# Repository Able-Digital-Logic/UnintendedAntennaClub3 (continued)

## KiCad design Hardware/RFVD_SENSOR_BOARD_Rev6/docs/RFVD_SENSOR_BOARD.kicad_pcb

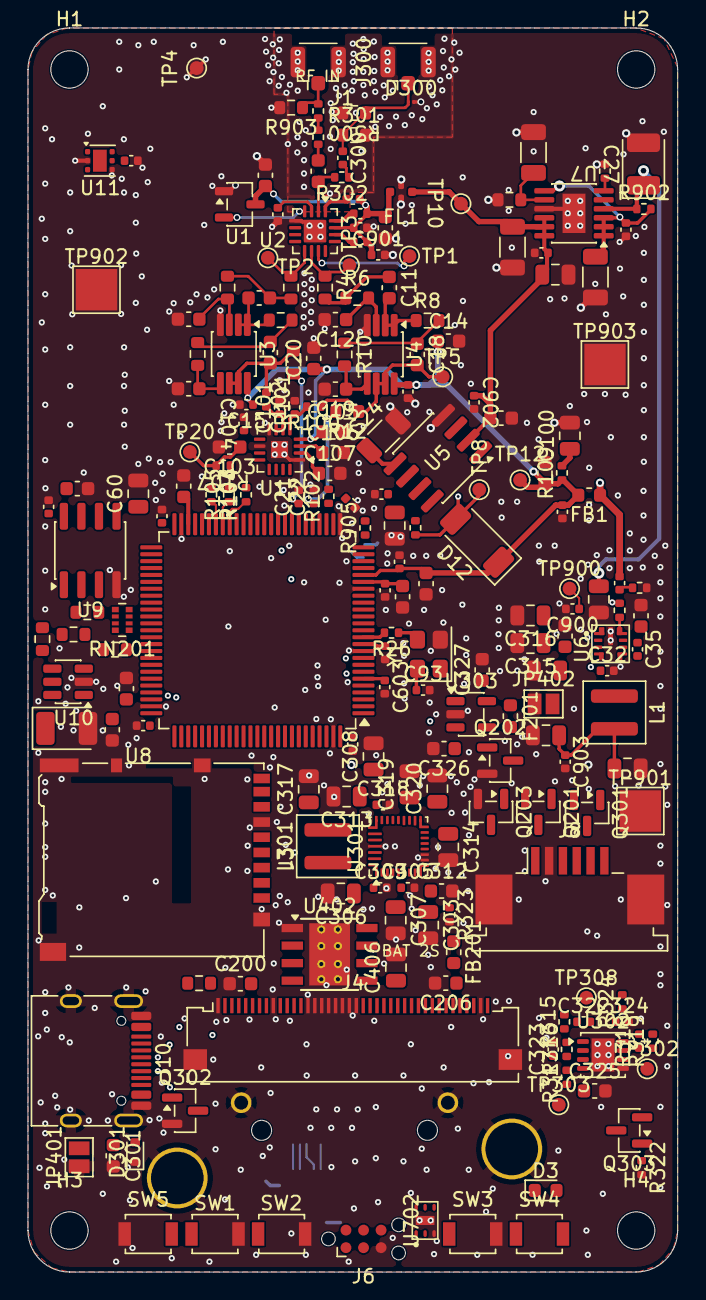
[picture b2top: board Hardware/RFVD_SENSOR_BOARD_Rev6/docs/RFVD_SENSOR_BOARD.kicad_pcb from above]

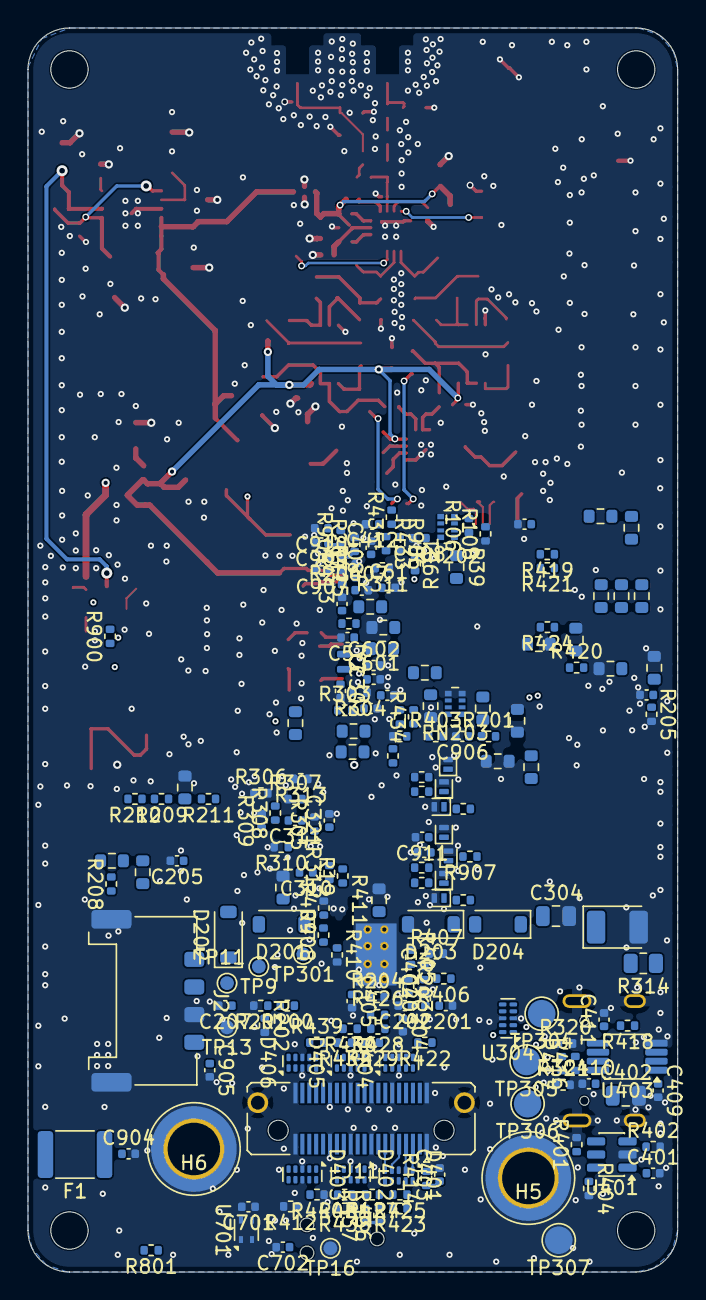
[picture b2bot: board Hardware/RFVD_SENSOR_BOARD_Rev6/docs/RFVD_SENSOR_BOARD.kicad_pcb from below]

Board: 6 copper layers, 47.0 x 90.0 mm, 409 parts (193 on the bottom side), 247 nets.

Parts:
C1, C33: 100nF; C_0603_1608Metric
C2: 47pF C0G 1% 100V; C_0603_1608Metric
C3, C4: 100pF; C_0402_1005Metric
C5, C23, C37, C44, C51, C59, C65, C103, C105, C106, C107, C301, C326: 1uF; C_0603_1608Metric
C6, C8, C321, C412: 1nF; C_0402_1005Metric
C7, C26, C29, C35, C40, C45, C46, C47, C48, C50, C53, C54, C55, C56, C57, C58, C61, C62, C64, C93, C104, C302, C305, C309, C318, C322, C323, C324, C401, C403, C404, C407, C408, C409, C410, C411, C603, C701, C702: 100nF; C_0402_1005Metric
C9, C11: 510p; C_0603_1608Metric
C10, C12, C17, C19: 470p; C_0603_1608Metric
C13, C15: 100n; C_0402_1005Metric
C14, C20: 1u; C_0603_1608Metric
C16, C18: 1.2n; C_0603_1608Metric
C21, C22: 1.5nF C0G 2% 50V; C_0402_1005Metric
C24: 1uF 25V film; C_1206_3216Metric
C25: 4.7uF; C_0805_2012Metric
C27: 22uF 25V polymer; CP_EIA-3528-21_Kemet-B
C28, C30, C38, C303, C304, C306, C307, C308, C313, C314, C315, C316, C317, C319, C320, C402, C406: 10uF; C_0805_2012Metric
C31: 10uF; C_1206_3216Metric
C32, C67, C70, C71, C205, C901, C902, C903, C904: 100nF 25V X7R; C_0402_1005Metric
C34: 470nF; C_1206_3216Metric
C36: 22uF; C_1206_3216Metric
C39, C42, C100: 22uF; C_0805_2012Metric
C41: 22pF; C_0402_1005Metric
C49, C52: 2.2uF; C_0603_1608Metric
C60: 10uF 16V X7R; C_0805_2012Metric
C63: 47uF POLY; CP_EIA-3528-21_Kemet-B
C66: 1uF 25V X7R; C_0603_1608Metric
C68: 47uF 10V POLY; CP_EIA-3528-21_Kemet-B
C69, C201: 100nF 25V; C_0402_1005Metric
C101, C102: 2.2nF C0G; C_0402_1005Metric
C200, C206: 1uF 25V; C_0603_1608Metric
C202, C203, C900: 47pF 50V C0G; C_0402_1005Metric
C204: DNP 47pF C0G; C_0402_1005Metric
C207: 100pF 50V C0G; C_0402_1005Metric
C300, C905, C906, C907: 1nF C0G 50V; C_0402_1005Metric
C310, C311, C405: 47nF; C_0402_1005Metric
C312, C327: 4.7uF; C_0603_1608Metric
C325: 330nF; C_0603_1608Metric
C601, C602: 10pF C0G; C_0402_1005Metric
C908, C909, C910: 100pF C0G 50V; C_0402_1005Metric
C911: 15pF C0G 50V; C_0402_1005Metric
D1, D300: PESD5V0H1BSF; PESD2V5Y1BSF_SOD962-2_ManufacturerLand
D3: GREEN LED; LED_0603_1608Metric
D4, D5, D6, D7, D8, D9, D10: 5V ESD 2pF; D_SOD-882
D12: PMEG6030EP; D_SOD-128
D201, D202, D203, D204: NSI45020A; D_SOD-123
D301: TPD1E10B06DYAR; D_SOD-523
D401, D402, D403, D404, D405, D406: TPD4E05U06DQAR; USON-10_2.5x1.0mm_P0.5mm
F1: MF-MSMF150/24X-2; Fuse_1812_4532Metric
F201: 200mA PTC; Fuse_0603_1608Metric
FB1: 600R@100MHz 500mA; L_0603_1608Metric
FB201: 600R@100MHz; L_0603_1608Metric
FL1: NFM18PC104R1C3D; Murata_NFM18PC_0603_3T
H1, H2, H3, H4: MountingHole_2.7mm
H5, H6: BSMTSOM250BTR; Standoff_SMT_M2_BZXC_BSMTSOM2_Hole3.8mm_Pad6.2mm
J1: AIMD_IN; U.FL_Hirose_U.FL-R-SMT-1_Vertical
J2: 2053380004; Molex_Pico-Lock_205338-0004_1x04-1MP_P2.00mm_Horizontal
J3: DM3AT-SF-PEJM5; microSD_HC_Hirose_DM3AT-SF-PEJM5
J4: XF2M-4015-1A; Omron_XF2M-4015-1A_1x40-1MP_P0.5mm_Horizontal
J6: TC2030-NL SWD POGO DNP; Tag-Connect_TC2030-IDC-NL_2x03_P1.27mm_Vertical
J8: 84953-6; TE_84953-6_1x06-1MP_P1.0mm_Horizontal
J10: TYPE-C-31-M-12; USB_C_Receptacle_HRO_TYPE-C-31-M-12
J11: LSHM-120-02.5-L-DV-A-N-K-TR; Samtec_LSHM-120-xx.x-x-DV-S_2x20-1SH_P0.50mm_Vertical
J300: CAL_IN; U.FL_Hirose_U.FL-R-SMT-1_Vertical
JP401, JP402: SJ open; SolderJumper-2_P1.3mm_Open_Pad1.0x1.5mm
L1: 4.7uH; L_Coilcraft_XAL4020-XXX
L301: 1uH; L_Coilcraft_XAL4020-XXX
Q201, Q303: AO3401A; SOT-23
Q202, Q302: 2N7002; SOT-23
Q203, Q301: AO3400A; SOT-23
R1, R2, R410: 1.50k; R_0402_1005Metric
R3, R4, R5, R6: 2.26k; R_0603_1608Metric
R7, R8, R9, R10: 1.33k; R_0603_1608Metric
R11, R12: 47R; R_0603_1608Metric
R13, R902, R907: 1R 1%; R_0402_1005Metric
R14: 49.9k; R_0603_1608Metric
R15, R19, R206, R801, R901: 1k 1%; R_0402_1005Metric
R16, R413: 33.2k; R_0402_1005Metric
R17: 14.3k; R_0402_1005Metric
R18, R20, R38, R203, R204, R205, R208, R210: 10k 1%; R_0402_1005Metric
R21, R24, R25, R41, R51, R52: 100k 0.1%; R_0603_1608Metric
R22: 20.0k 0.1%; R_0603_1608Metric
R23: 10k; R_0603_1608Metric
R26: 33R 1%; R_0402_1005Metric
R27, R28, R29, R36, R37: 47k 1%; R_0402_1005Metric
R30, R31, R32, R33, R34, R35, R39, R60, R61, R62, R63, R64, R65, R66, R67: 33R 1%; R_0603_1608Metric
R40, R44, R48, R49, R50: 10k 1%; R_0603_1608Metric
R42, R45: 4.7k 1%; R_0603_1608Metric
R43: 66.5k 1%; R_0603_1608Metric
R53, R54: 4.7k 1%; R_0402_1005Metric
R100, R101, R104, R105, R106, R107, R419, R420, R421, R423, R424, R433: 33R; R_0402_1005Metric
R102, R109: 1R; R_0402_1005Metric
R103, R313, R317, R318, R434: 100R; R_0402_1005Metric
R108, R310, R311, R312, R403, R416, R701: 10k; R_0402_1005Metric
R200, R201, R202, R405: 0R; R_0402_1005Metric
R207, R209, R322, R323, R324: 100k 1%; R_0402_1005Metric
R211: 100R 1%; R_0402_1005Metric
R300, R301: 100R; R_0603_1608Metric
R302: 3.32k; R_0402_1005Metric
R303, R304, R402, R407, R412, R414, R415, R436, R437, R438, R439, R440, R900: 100k; R_0402_1005Metric
R305: 6.04k; R_0402_1005Metric
R306: 51k; R_0402_1005Metric
R307: 20k; R_0402_1005Metric
R308, R320, R321: 5.23k; R_0402_1005Metric
R309: 30.1k; R_0402_1005Metric
R314: 0R; R_0805_2012Metric
R315: 160R; R_0402_1005Metric
R316: 261R; R_0402_1005Metric
R319, R408: 470k; R_0402_1005Metric
R401: 45.3k; R_0402_1005Metric
R404, R417, R418: 2.2k; R_0402_1005Metric
R406: 0R DNP; R_0402_1005Metric
R409: 73.2k; R_0402_1005Metric
R411: 1.5k; R_0603_1608Metric
R422, R435: 1k; R_0402_1005Metric
R425, R426, R427, R428, R429, R430, R431, R432: 330R; R_0402_1005Metric
R903: DNP; R_0603_1608Metric
R904, R905, R906: 330R 1%; R_0402_1005Metric
RN201, RN202, RN203: 47R x4; R_Array_Convex_4x0402
SW1: RECORD / STOP; SW_SPST_B3U-1000P
SW2: MARK; SW_SPST_B3U-1000P
SW3: RESET; SW_SPST_B3U-1000P
SW4: BOOT; SW_SPST_B3U-1000P
SW5: B3U-1000P; SW_SPST_B3U-1000P
TP1: VRMS_DIAG; TestPoint_Pad_D1.0mm
TP2: EREF_RAW; TestPoint_Pad_D1.0mm
TP3: VENV_RAW; TestPoint_Pad_D1.0mm
TP4: GND_ANALOG; TestPoint_Pad_D1.0mm
TP5: VENV_BUF; TestPoint_Pad_D1.0mm
TP8: +3V0_REF; TestPoint_Pad_D1.0mm
TP9: VSYS; TestPoint_Pad_D1.0mm
TP10: +5V_A; TestPoint_Pad_D1.0mm
TP11: +3V3_D; TestPoint_Pad_D1.0mm
TP12: +3V3_A; TestPoint_Pad_D1.0mm
TP13: GND_POWER; TestPoint_Pad_D1.0mm
TP16: GND_SERVICE; TestPoint_Pad_D1.0mm
TP20: EXTADC_REFIO; TestPoint_Pad_D1.0mm
TP301: CHG_STAT; TestPoint_Pad_D1.0mm
TP302: BAL_OVP; TestPoint_Pad_D1.0mm
TP303: VBAT_PACK; TestPoint_Pad_D1.0mm
TP304: POGO_VBUS; TestPoint_Pad_D2.0mm
TP305: POGO_D+; TestPoint_Pad_D2.0mm
TP306: POGO_D-; TestPoint_Pad_D2.0mm
TP307: POGO_GND; TestPoint_Pad_D2.0mm
TP308: BATT_MID; TestPoint_Pad_D1.0mm
TP900: BUCK_SYNC; TestPoint_Pad_D1.0mm
TP901, TP902, TP903: DISP_GND; TestPoint_Pad_3.0x3.0mm
U1: TLV809EA46DBZR; SOT-23-3
U2: ADL5511ACPZ-R7; LFCSP-16-1EP_3x3mm_P0.5mm_EP1.6x1.6mm
U3, U4: OPA2320; VSSOP-8_3x3mm_P0.65mm
U5: REF5030IDR; SOIC-8_3.9x4.9mm_P1.27mm
U6: LMR43620MB5RPER; TI_RPE0009B_VQFN-HR-9_2x2mm_Stencil
U7: LT3045EMSE#PBF (+5V_A); MSOP-12-1EP_3x4.039mm_P0.65mm_EP1.651x2.845mm
U8: STM32H743VIT6; LQFP-100_14x14mm_P0.5mm
U9: APS6404L-3SQR-SN; SOIC-8_3.9x4.9mm_P1.27mm
U10, U401: TPS2553DDBVR; SOT-23-6
U11: TMP117AIDRVR; TMP117_DRV_WSON6_NoPasteEP
U13: AD7380BCPZ-RL7; TQFN-16-1EP_3x3mm_P0.5mm_EP1.23x1.23mm
U301: BQ25798RQMR; Texas_RQM0029A_VQFN-29_4x4mm_P0.4mm
U302: BQ29209DRBR; VSON-8-1EP_3x3mm_P0.65mm_EP1.65x2.4mm
U303: TPS70933DBVR; SOT-23-5
U304: TPD4E05U06DQAR; USON-10_2.5x1.0mm_P0.5mm
U402: TPS259631DDAR; TI_SO-PowerPAD-8_ThermalVias
U403: TCA9517ADGKR; VSSOP-8_3x3mm_P0.65mm
U701: SHT40-AD1B-R2; Sensirion_DFN-4_1.5x1.5mm_P0.8mm_SHT4x_NoCentralPad
U702: OPT3004DNPR; TI_DNP0006A_USON-6-1EP_2x2mm_P0.65mm_EP0.65x1.35mm
Y1: 12MHz 3.3V CMOS; Oscillator_SMD_Abracon_ASE-4Pin_3.2x2.5mm
Y2: 32.768kHz 7pF; Crystal_SMD_Abracon_ABS05-2Pin_1.6x1.0mm

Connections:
+3V0_REF: C26.1, C56.1, C59.1, D12.2 (A), R13.1, R107.1, TP8.1 (1_1), U5.6 (Vout), U8.20 (VREF+)
+3V3_A: C13.1, C14.1, C15.1, C20.1, C44.1, C45.1, C48.1, C51.1, C105.1, D12.1 (K), FB1.2, R109.1, TP12.1 (1_1), U3.8 (V+), U4.8 (V+), U8.21 (VDDA), U13.4 (VCC)
+3V3_D: C39.1, C41.2, C42.1, C47.1, C50.1, C53.1, C54.1, C55.1, C58.1, C60.1, C64.1, C65.1, C66.1, C71.1, C93.1, C401.1, C409.1, C701.1, C702.1, C903.1, FB1.1, J6.1 (VCC), L1.2, R16.1, R18.1, R27.1, R28.1, R29.1, R36.1, R37.1, R38.1, R40.1, R44.1, R48.1, R49.1, R53.2, R54.2, R102.1, R108.1, R311.1, R403.1, R439.1, R701.2, R801.1, R900.2, R907.1, TP11.1 (1_1), U8.11 (VDD), U8.27 (VDD), U8.50 (VDD), U8.75 (VDD), U8.100 (VDD), U9.8 (VDD), U10.1 (IN), U11.5 (V+), U401.1 (IN), U403.1 (VCCA), U701.3 (VDD), U702.1 (VDD), U702.2 (ADDR), Y1.1 (EN), Y1.4 (Vdd)
+3V3_EXP: C402.1, C403.1, C410.1, J11.3, J11.4, J11.37, J11.38, R404.1, R414.1, R416.1, R417.1, R418.1, R436.1, R437.1, U401.6 (OUT), U403.8 (VCCB)
+3V3_UI: C68.1, C69.1, C200.2, C201.2, C205.1, J4.7, J4.8, J8.1, R42.1, R45.1, R50.1, R200.1, R203.1, R204.1, R205.1, R208.1, U10.6 (OUT)
+5V_A: C23.1, C36.1, C38.1, C40.1, C902.1, FL1.1, R24.1, TP10.1 (1_1), U5.2 (Vin), U7.10 (OUTS), U7.11 (OUT), U7.12 (OUT)
/Battery and power/A3V3_DAMP: C100.1, R109.2
/Battery and power/BUCK_VCC: C37.1, U6.7 (VCC)
/Battery and power/LT5_ILIM: R15.1, U7.6 (ILIM)
/Battery and power/VSYS_LDO: C29.1, C31.1, R902.2, U7.1 (IN), U7.2 (IN), U7.3 (IN), U7.7 (PGFB)
/Battery, charger and USB-C/BAL_OVP: R324.1, TP302.1 (1_1), U302.8 (OUT)
/Battery, charger and USB-C/BATP: R313.2, U301.18 (BATP)
/Battery, charger and USB-C/BATT_MID: J2.2, R316.1, R317.1, TP308.1 (1_1)
/Battery, charger and USB-C/BATT_NTC: C905.1, J2.4, R308.2, R309.1, R310.1, U301.16 (TS)
/Battery, charger and USB-C/B_VC1: C322.2, C323.1, R316.2, U302.2 (VC1)
/Battery, charger and USB-C/B_VC2: C322.1, R315.2, U302.1 (VC2)
/Battery, charger and USB-C/B_VCB: R317.2, U302.3 (VC1_CB)
/Battery, charger and USB-C/B_VDD: C324.1, R318.2, R319.1, U302.7 (VDD)
/Battery, charger and USB-C/CC1: J10.A5 (CC1), R320.1, U304.4 (D2+)
/Battery, charger and USB-C/CC2: J10.B5 (CC2), R321.1, U304.5 (D2-)
/Battery, charger and USB-C/CHG_BAT: C319.1, C320.1, Q301.2 (S), R314.1, U301.22 (BAT), U301.23 (BAT)
/Battery, charger and USB-C/CHG_LED_A: D3.2 (A), R19.2
/Battery, charger and USB-C/CHG_STAT: D3.1 (K), R312.2, TP301.1 (1_1), U301.1 (STAT)
/Battery, charger and USB-C/ILIM_HIZ: R306.2, R307.1, U301.17 (ILIM_HIZ)
/Battery, charger and USB-C/PACK_FUSED: F1.1, Q303.3 (D)
/Battery, charger and USB-C/PROG: R305.1, U301.20 (PROG)
/Battery, charger and USB-C/QON_N: SW5.2, U301.12 (~QON)
/Battery, charger and USB-C/REGN: C312.1, R19.1, R306.1, R308.1, R312.1, U301.5 (REGN)
/Battery, charger and USB-C/SDRV: C321.1, Q301.1 (G), U301.24 (SDRV)
/Expansion mezzanine/EXP_ANA_MON: D406.5 (D2-), J11.34, R435.2
/Expansion mezzanine/EXP_DETECT_N: D405.1 (D1+), J11.32, R432.2, R439.2
/Expansion mezzanine/EXP_GATE: D403.1 (D1+), J11.33, R433.2
/Expansion mezzanine/EXP_I2C_SCL: D402.2 (D1-), J11.25, R417.2, U403.7 (SCLB)
/Expansion mezzanine/EXP_I2C_SDA: D402.4 (D2+), J11.27, R418.2, U403.6 (SDAB)
/Expansion mezzanine/EXP_INT0_N: D404.1 (D1+), J11.14, R426.2
/Expansion mezzanine/EXP_INT1_N: D405.5 (D2-), J11.16, R428.2
/Expansion mezzanine/EXP_IO0: D405.4 (D2+), J11.26, R429.2
/Expansion mezzanine/EXP_IO1: D405.2 (D1-), J11.28, R430.2
/Expansion mezzanine/EXP_RST_N: D402.5 (D2-), J11.31, R431.2, R438.2
/Expansion mezzanine/EXP_SPI_CS0_N: D401.5 (D2-), J11.13, R425.2, R436.2
/Expansion mezzanine/EXP_SPI_CS1_N: D402.1 (D1+), J11.15, R427.2, R437.2
/Expansion mezzanine/EXP_SPI_MISO: D401.4 (D2+), J11.9, R423.2
/Expansion mezzanine/EXP_SPI_MOSI: D401.2 (D1-), J11.7, R421.2
/Expansion mezzanine/EXP_SPI_SCK: D401.1 (D1+), J11.5, R419.2
/Expansion mezzanine/EXP_SYNC: D403.2 (D1-), J11.35, R434.2, R440.2
/Expansion mezzanine/EXP_TMR0: D404.5 (D2-), J11.6, R420.2
/Expansion mezzanine/EXP_TMR1: D404.2 (D1-), J11.10, R424.2
/Expansion mezzanine/EXP_TMR_IN: D404.4 (D2+), J11.8, R422.2
/Expansion mezzanine/EXP_VHP_IN: C404.1, R405.2, R406.2, R408.1, U402.4 (VIN)
/Expansion mezzanine/EXP_VHP_OVLO: R408.2, R409.1, U402.8 (OVLO/OVCSEL)
/External ADC/ADC_AIN_EREF: C101.1, R101.2, U13.6 (AINB+/AINB0), U13.7 (AINA-/AINA1)
/External ADC/ADC_AIN_VENV: C102.1, R100.2, U13.5 (AINB-/AINB1)
/External ADC/ADC_CS_N_U13: R106.2, U13.12 (~CS)
/External ADC/ADC_REFCAP: C104.1, U13.9 (REFCAP)
/External ADC/ADC_REFIO: C103.1, R107.2, TP20.1 (1_1), U13.11 (REFIO)
/External ADC/ADC_SCLK_U13: R104.2, U13.16 (SCLK)
/External ADC/ADC_SDI_U13: R105.2, U13.15 (SDI)
/External ADC/ADC_SDOA_U13: R103.1, U13.13 (SDOA)
/External ADC/ADC_VLOGIC: C107.1, R102.2, U13.2 (VLOGIC)
/RF input and detector/+5V_RF: C1.1, C3.1, C5.1, C6.2, C7.2, C8.2, C901.1, FL1.3, U1.3 (VDD), U2.15 (VPOS)
/RF input and detector/CAL_IN: C300.1, D300.1 (A1), J300.1 (In), R300.1, R301.1
/RF input and detector/CAL_INJ: C300.2, R302.1
/RF input and detector/RFIN: C2.2, D1.1 (A1), R302.2, U2.2 (RFIN)
/RF input and detector/VRMS_DIAG: TP1.1 (1_1), U2.11 (VRMS)
/SD and capture memory/+3V3_SD: C62.1, C63.1, J3.4 (VDD), R907.2
/SD and capture memory/PSRAM_IO0: R60.2, R61.1
/SD and capture memory/PSRAM_IO0_RAM: R61.2, U9.5 (SI/SIO0)
/SD and capture memory/PSRAM_IO1: R62.2, R63.1
/SD and capture memory/PSRAM_IO1_RAM: R63.2, U9.2 (SO/SIO1)
/SD and capture memory/PSRAM_IO2: R64.2, R65.1
/SD and capture memory/PSRAM_IO2_RAM: R65.2, U9.3 (SIO2)
/SD and capture memory/PSRAM_IO3: R66.2, R67.1
/SD and capture memory/PSRAM_IO3_RAM: R67.2, U9.7 (SIO3)
/SD and capture memory/SD_CLK: C911.1, D7.1 (K), J3.5 (CLK), R33.2
/SD and capture memory/SD_CMD: D6.1 (K), J3.3 (CMD), R29.2, R32.2
/SD and capture memory/SD_D0: D8.1 (K), J3.7 (DAT0), R34.2, R36.2
/SD and capture memory/SD_D1: D9.1 (K), J3.8 (DAT1), R35.2, R37.2
/SD and capture memory/SD_D2: D4.1 (K), J3.1 (DAT2), R27.2, R30.2
/SD and capture memory/SD_D3: D5.1 (K), J3.2 (DAT3/CD), R28.2, R31.2
/STM32H743 controller/BUCK_SYNC_MCU: R901.1, U8.35 (PB1)
/STM32H743 controller/LCD_RST_MCU: C909.1, R904.1, U8.24 (PA2)
/STM32H743 controller/TP_INT_MCU: C908.1, R906.1, U8.31 (PA7)
/STM32H743 controller/TP_RST_MCU: C910.1, R905.1, U8.25 (PA3)
/STM32H743 controller/VCAP: C49.1, C52.1, U8.48 (VCAP), U8.73 (VCAP)
/Screen and controls/LCD_BL_SW: D201.1 (K), D202.1 (K), D203.1 (K), D204.1 (K), Q203.3 (D)
/Screen and controls/LCD_CS_N: C203.1, J4.10, R50.2, RN203.6 (R3.2)
/Screen and controls/LCD_D0: J4.22, RN201.8 (R1.2)
/Screen and controls/LCD_D1: J4.23, RN201.7 (R2.2)
/Screen and controls/LCD_D2: J4.24, RN201.6 (R3.2)
/Screen and controls/LCD_D3: J4.25, RN201.5 (R4.2)
/Screen and controls/LCD_D4: J4.26, RN202.8 (R1.2)
/Screen and controls/LCD_D5: J4.27, RN202.7 (R2.2)
/Screen and controls/LCD_D6: J4.28, RN202.6 (R3.2)
/Screen and controls/LCD_D7: J4.29, RN202.5 (R4.2)
/Screen and controls/LCD_DC: J4.11, RN203.5 (R4.2)
/Screen and controls/LCD_IM0: J4.31, R200.2
/Screen and controls/LCD_IM1: J4.32, R201.1
/Screen and controls/LCD_IM2: J4.33, R202.1
/Screen and controls/LCD_LED_A: C206.1, C207.1, FB201.2, J4.38
/Screen and controls/LCD_LED_K1: D201.2 (A), J4.34
/Screen and controls/LCD_LED_K2: D202.2 (A), J4.35
/Screen and controls/LCD_LED_K3: D203.2 (A), J4.36
/Screen and controls/LCD_LED_K4: D204.2 (A), J4.37
/Screen and controls/LCD_RD_N: C204.1, J4.13, R204.2, RN203.7 (R2.2)
/Screen and controls/LCD_TE: J4.40, R206.2
/Screen and controls/LCD_WR_N: C202.1, J4.12, R203.2, RN203.8 (R1.2)
ADC_EREF: C21.1, R11.2, U8.32 (PC4)
ADC_VENV: C22.1, R12.2, U8.30 (PA6)
BOOT0: R20.1, SW4.1, U8.94 (BOOT0)
BUCK_SYNC: C900.1, R900.1, R901.2, TP900.1 (1_1), U6.1 (MODE_SYNC)
CHG_CE: R323.1, R324.2, U301.13 (~CE)
CHG_INT_N: C907.1, R311.2, U8.22 (PA0), U301.21 (~INT)
EREF_BUF: C16.2, R11.1, R101.1, U3.6 (-), U3.7 (OUT)
EREF_RAW: R3.1, TP2.1 (1_1), U2.9 (EREF)
EXP_3V3_EN: JP401.2 (B), R402.1, U8.45 (PE15), U401.3 (EN)
EXP_3V3_SNS: C408.1, R414.2, R415.1, U8.18 (PC3_C)
EXP_ANA_MON_MCU: C412.1, R435.1, U8.28 (PA4)
EXP_CS0_N_MCU: R425.1, U8.51 (PB12)
EXP_CS1_N_MCU: R427.1, U8.55 (PD8)
EXP_DETECT_N_MCU: R432.1, U8.90 (PB4)
EXP_FAULT_N: R403.2, U8.87 (PD6), U401.4 (~FAULT), U402.6 (~FLT)
EXP_GATE_MCU: R433.1, U8.29 (PA5)
EXP_INT0_N_MCU: R426.1, U8.56 (PD9)
EXP_INT1_N_MCU: R428.1, U8.57 (PD10)
EXP_IO0_MCU: R429.1, U8.98 (PE1)
EXP_IO1_MCU: R430.1, U8.97 (PE0)
EXP_MISO_MCU: R423.1, U8.53 (PB14)
EXP_MOSI_MCU: R421.1, U8.54 (PB15)
EXP_RST_N_MCU: R431.1, U8.91 (PB5)
EXP_SCK_MCU: R419.1, U8.52 (PB13)
EXP_SYNC_MCU: R434.1, U8.93 (PB7)
EXP_TMR0_MCU: R420.1, U8.67 (PA8)
EXP_TMR1_MCU: R424.1, U8.64 (PC7)
EXP_TMR_IN_MCU: R422.1, U8.77 (PA15)
EXP_VHP: C406.1, J11.19, J11.20, J11.21, J11.22, R411.1, R412.1, U402.5 (OUT)
EXP_VHP_EN: JP402.2 (B), R407.1, U8.13 (PH1), U402.3 (EN/UVLO)
EXP_VHP_SNS: C407.1, R412.2, R413.1, U8.17 (PC2_C)
EXTADC_CS_N: R106.1, R108.2, U8.41 (PE11)
EXTADC_SCLK: R104.1, U8.42 (PE12)
EXTADC_SDI: R105.1, U8.43 (PE13)
EXTADC_SDOA: R103.2, U8.44 (PE14)
GND: C1.2, C3.2, C4.2, C5.2, C10.2, C12.2, C13.2, C14.2, C15.2, C17.2, C19.2, C20.2, C21.2, C22.2, C23.2, C24.2, C25.2, C26.2, C27.2, C28.2, C29.2, C30.2, C31.2, C32.2, C33.2, C34.2, C36.2, C37.2, C38.2, C39.2, C40.2, C42.2, C44.2, C45.2, C46.2, C47.2, C48.2, C49.2, C50.2, C51.2, C52.2, C53.2, C54.2, C55.2, C56.2, C57.2, C58.2, C59.2, C60.2, C61.2, C62.2, C63.2, C64.2, C65.2, C66.2, C67.2, C68.2, C69.2, C70.2, C71.2, C93.2, C100.2, C101.2, C102.2, C103.2, C104.2, C105.2, C106.2, C107.2, C200.1, C201.1, C202.2, C203.2, C204.2, C205.2, C206.2, C207.2, C301.2, C302.1, C303.2, C304.2, C305.2, C306.2, C307.2, C308.2, C309.2, C312.2, C313.2, C314.2, C315.2, C316.2, C317.2, C318.2, C319.2, C320.2, C321.2, C323.2, C324.2, C325.2, C326.2, C327.2, C401.2, C402.2, C403.2, C404.2, C405.2, C406.2, C407.2, C408.2, C409.2, C410.2, C411.2, C412.2, C601.2, C602.2, C603.2, C701.2, C702.2, C900.2, C901.2, C902.2, C903.2, C904.2, C905.2, C906.2, C907.2, C908.2, C909.2, C910.2, C911.2, D1.2 (A2), D4.2 (A), D5.2 (A), D6.2 (A), D7.2 (A), D8.2 (A), D9.2 (A), D10.2 (A), D300.2 (A2), D301.1 (A1), D401.3 (GND), D401.8 (GND), D402.3 (GND), D402.8 (GND), D403.3 (GND), D403.8 (GND), D404.3 (GND), D404.8 (GND), D405.3 (GND), D405.8 (GND), D406.3 (GND), D406.8 (GND), FL1.2, H5.1 (1_1), H6.1 (1_1), J1.2 (Ext), J2.3, J2.MP (MountPin), J3.6 (VSS), J3.10 (DET_A), J3.SH (SHIELD), J4.1, J4.9, J4.14, J4.15, J4.16, J4.17, J4.18, J4.19, J4.20, J4.21, J4.39, J4.MP (MountPin), J6.5 (GND), J8.2, J8.MP (MountPin), J10.A1 (GND), J10.A12 (GND), J10.B1 (GND), J10.B12 (GND), J10.SH (SHIELD), J11.1, J11.2, J11.11, J11.12, J11.17, J11.18, J11.23, J11.24, J11.29, J11.30, J11.39, J11.40, J11.SH (Shield), J300.2 (Ext), JP401.1 (A), JP402.1 (A), Q202.2 (S), Q203.2 (S), Q302.2 (S), R14.2, R15.2, R17.1, R20.2, R22.2, R25.2, R41.2, R43.2, R51.2, R52.2, R201.2, R202.2, R205.2, R207.2, R300.2, R301.2, R304.1, R305.2, R307.2, R309.2, R310.2, R320.2, R321.2, R322.2, R323.2, R401.2, R402.2, R404.2, R407.2, R409.2, R410.2, R411.2, R413.2, R415.2, R438.1, R440.1, R903.2, SW1.2, SW2.2, SW3.2, SW5.1, TP4.1 (1_1), TP13.1 (1_1), TP16.1 (1_1), TP307.1 (1_1), TP901.1 (1_1), TP902.1 (1_1), TP903.1 (1_1), U1.1 (GND), U2.5 (COMM), U2.17 (EP), U3.4 (V-), U4.4 (V-), U5.4 (GND), U6.9 (GND), U7.9 (GND), U7.13 (GND), U8.10 (VSS), U8.19 (VSSA), U8.26 (VSS), U8.49 (VSS), U8.74 (VSS), U8.99 (VSS), U9.4 (VSS), U10.2 (GND), U11.2 (GND), U11.4 (ADD0), U13.1 (GND), U13.8 (AINA+/AINA0), U13.10 (GND), U13.17 (EP), U301.10 (ACDRV2), U301.11 (ACDRV1), U301.27 (GND), U302.5 (GND), U302.9 (PAD), U303.2 (GND), U304.3 (GND), U304.8 (GND), U401.2 (GND), U402.1 (GND), U402.9 (GND), U403.4 (GND), U701.4 (VSS), U702.3 (GND), U702.7 (EP), Y1.2 (GND)
I2C_SCL: R53.1, U8.95 (PB8), U11.1 (SCL), U301.14 (SCL), U403.2 (SCLA), U701.2 (SCL), U702.4 (SCL)
I2C_SDA: R54.1, U8.96 (PB9), U11.6 (SDA), U301.15 (SDA), U403.3 (SDAA), U701.1 (SDA), U702.6 (SDA)
LCD_BL: R211.1, U8.63 (PC6)
LCD_CS_N_MCU: RN203.3 (R3.1), U8.88 (PD7)
LCD_D0_MCU: RN201.1 (R1.1), U8.61 (PD14)
LCD_D1_MCU: RN201.2 (R2.1), U8.62 (PD15)
LCD_D2_MCU: RN201.3 (R3.1), U8.81 (PD0)
LCD_D3_MCU: RN201.4 (R4.1), U8.82 (PD1)
LCD_D4_MCU: RN202.1 (R1.1), U8.37 (PE7)
LCD_D5_MCU: RN202.2 (R2.1), U8.38 (PE8)
LCD_D6_MCU: RN202.3 (R3.1), U8.39 (PE9)
LCD_D7_MCU: RN202.4 (R4.1), U8.40 (PE10)
LCD_DC_MCU: RN203.4 (R4.1), U8.5 (PE6)
LCD_RD_N_MCU: RN203.2 (R2.1), U8.85 (PD4)
LCD_RST: J4.30, R51.1, R904.2
LCD_TE_MCU: R206.1, R207.1, U8.23 (PA1)
LCD_WR_N_MCU: RN203.1 (R1.1), U8.86 (PD5)
LID_INT: C906.1, R701.1, U8.84 (PD3), U702.5 (INT)
MARK_N: C70.1, R49.2, SW2.1, U8.3 (PE4)
NRST: C46.1, J6.3 (~RESET), R18.2, SW3.1, U8.14 (NRST)
unnamed: C2.1, R2.2
unnamed: C9.1, R3.2, R5.1
unnamed: C11.1, R4.2, R6.1
unnamed: C16.1, R7.2, R9.1
unnamed: C18.1, R8.2, R10.1
unnamed: C25.1, R13.2
unnamed: J1.1 (In), R1.2, R903.1
unnamed: F1.2, J2.1
unnamed: FB201.1, Q201.3 (D)
unnamed: Q201.1 (G), R209.2, R210.1
unnamed: F201.2, Q201.2 (S), R209.1
unnamed: Q202.3 (D), R210.2
unnamed: Q203.1 (G), R52.1, R211.2
unnamed: Q302.3 (D), R319.2, U302.6 (~CB_EN)
unnamed: Q303.1 (G), R322.1
unnamed: R1.1, R2.1
unnamed: R21.2, R22.1, R23.1
unnamed: R801.2, SW4.2
unnamed: U1.2 (RESET_n), U2.4 (ENBL)
unnamed: C4.1, U2.3 (FLT1)
unnamed: C6.1, U2.16 (FLT2)
unnamed: C8.1, U2.1 (FLT3)
unnamed: C7.1, U2.14 (FLT4)
unnamed: C10.1, R5.2, U3.3 (+)
unnamed: C9.2, R7.1, U3.1 (OUT), U3.2 (-)
unnamed: C17.1, R9.2, U3.5 (+)
unnamed: C12.1, R6.2, U4.3 (+)
unnamed: C11.2, R8.1, U4.1 (OUT), U4.2 (-)
unnamed: C19.1, R10.2, U4.5 (+)
unnamed: C24.1, U5.5 (Trim/NR)
unnamed: C35.1, U6.6 (BOOT)
unnamed: C35.2, L1.1, U6.5 (SW)
unnamed: C41.1, R16.2, R17.2, U6.8 (VOUT_FB)
unnamed: C34.1, R14.1, U7.8 (SET)
unnamed: C57.1, R23.2, U8.15 (PC0)
unnamed: C61.1, R24.2, R25.1, U8.16 (PC1)
unnamed: C601.1, U8.8 (PC14), Y2.2
unnamed: C602.1, U8.9 (PC15), Y2.1
unnamed: R26.2, U8.12 (PH0)
unnamed: R39.2, U9.6 (SCLK)
unnamed: R43.1, U10.5 (ILIM)
unnamed: C106.1, U13.3 (REGCAP)
unnamed: C310.1, U301.4 (BTST1)
unnamed: C311.1, U301.19 (BTST2)
unnamed: C306.1, C307.1, C308.1, C309.1, U301.29 (PMID)
unnamed: C310.2, L301.1, U301.28 (SW1)
unnamed: C311.2, L301.2, U301.26 (SW2)
unnamed: C325.1, U302.4 (CD)
unnamed: R401.1, U401.5 (ILIM)
unnamed: R410.1, U402.7 (ILM)
unnamed: C405.1, U402.2 (dV/dT)
unnamed: C411.1, R416.2, U403.5 (EN)
unnamed: R26.1, Y1.3 (OUT)
PSRAM_CLK_MCU: R39.1, U8.36 (PB2)
PSRAM_CS_N: R40.2, U8.92 (PB6), U9.1 (~CE)
PSRAM_IO0_MCU: R60.1, U8.58 (PD11)
PSRAM_IO1_MCU: R62.1, U8.59 (PD12)
PSRAM_IO2_MCU: R64.1, U8.1 (PE2)
PSRAM_IO3_MCU: R66.1, U8.60 (PD13)
RECORD_N: C67.1, R44.2, SW1.1, U8.2 (PE3)
SD_CD_N: D10.1 (K), J3.9 (DET_B), R38.2, U8.4 (PE5)
SD_CLK_MCU: R33.1, U8.80 (PC12)
SD_CMD_MCU: R32.1, U8.83 (PD2)
SD_D0_MCU: R34.1, U8.65 (PC8)
SD_D1_MCU: R35.1, U8.66 (PC9)
SD_D2_MCU: R30.1, U8.78 (PC10)
SD_D3_MCU: R31.1, U8.79 (PC11)
SWCLK: J6.4 (SWCLK), U8.76 (PA14)
SWDIO: J6.2 (SWDIO), U8.72 (PA13)
SWO: J6.6 (SWO), U8.89 (PB3)
TP_INT: J8.5, R208.2, R906.2
TP_RST: J8.6, R905.2
TP_SCL: J8.3, R45.2, U8.46 (PB10)
TP_SDA: J8.4, R42.2, U8.47 (PB11)
UI_EN: Q202.1 (G), R41.1, U8.33 (PC5), U10.3 (EN)
UI_FAULT_N: R48.2, U8.34 (PB0), U10.4 (~FAULT)
USB_DM: J10.A7 (D-), J10.B7 (D-), TP306.1 (1_1), U8.70 (PA11), U301.7 (D-), U304.2 (D1-)
USB_DP: J10.A6 (D+), J10.B6 (D+), TP305.1 (1_1), U8.71 (PA12), U301.6 (D+), U304.1 (D1+)
VBAT_PACK: C326.1, C904.1, Q301.3 (D), Q303.2 (S), R313.1, R314.2, R315.1, R318.1, TP303.1 (1_1), U303.1 (IN)
VBAT_RTC: C327.1, C603.1, U8.6 (VBAT), U303.5 (OUT)
VBUS: C301.1, C303.1, C304.1, C305.1, D301.2 (A2), J10.A4 (VBUS), J10.A9 (VBUS), J10.B4 (VBUS), J10.B9 (VBUS), Q302.1 (G), R303.2, R406.1, TP304.1 (1_1), U301.2 (VBUS), U301.3 (VBUS), U301.8 (VAC2), U301.9 (VAC1)
VBUS_DET: C302.2, R303.1, R304.2, U8.7 (PC13)
VENV_BUF: C18.2, R12.1, R100.1, TP5.1 (1_1), U4.6 (-), U4.7 (OUT)
VENV_RAW: R4.1, TP3.1 (1_1), U2.10 (VENV)
VSYS: C27.1, C28.1, C30.1, C32.1, C33.1, C313.1, C314.1, C315.1, C316.1, C317.1, C318.1, F201.1, R21.1, R405.1, R902.1, TP9.1 (1_1), U6.3 (EN_UVLO), U6.4 (VIN), U7.4 (EN/UV), U301.25 (SYS)

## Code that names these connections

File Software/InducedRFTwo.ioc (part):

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Mcu.Name=STM32L4S5VITx
Mcu.Package=LQFP100
Mcu.UserName=STM32L4S5VITx
PA0.GPIOParameters=GPIO_ModeDefaultPP,GPIO_Speed,GPIO_PuPd,GPIO_Label
PA0.GPIO_Label=ARD_D1 [UART4_TX]
PA0.GPIO_ModeDefaultPP=GPIO_MODE_AF_PP
PA0.GPIO_PuPd=GPIO_NOPULL
PA0.GPIO_Speed=GPIO_SPEED_FREQ_VERY_HIGH
PA0.Signal=UART4_TX
PA1.GPIOParameters=GPIO_ModeDefaultPP,GPIO_Speed,GPIO_PuPd,GPIO_Label
PA1.GPIO_Label=ARD_D0 [UART4_RX]
PA1.GPIO_ModeDefaultPP=GPIO_MODE_AF_PP
PA1.GPIO_PuPd=GPIO_NOPULL
PA1.GPIO_Speed=GPIO_SPEED_FREQ_VERY_HIGH
PA1.Signal=UART4_RX
PA13\ (JTMS/SWDIO).GPIOParameters=GPIO_Label
PA13\ (JTMS/SWDIO).GPIO_Label=SYS_JTMS_SWDIO
PA13\ (JTMS/SWDIO).Signal=SYS_JTMS-SWDIO
PA14\ (JTCK/SWCLK).GPIOParameters=GPIO_Label
PA14\ (JTCK/SWCLK).GPIO_Label=SYS_JTCK_SWCLK
PA14\ (JTCK/SWCLK).Signal=SYS_JTCK-SWCLK
PA15\ (JTDI).GPIOParameters=GPIO_Label
PA15\ (JTDI).GPIO_Label=BtnB
PA15\ (JTDI).Signal=GPIO_Input
PA2.GPIOParameters=GPIO_Speed,PinState,GPIO_PuPd,GPIO_Label,GPIO_ModeDefaultOutputPP
PA2.GPIO_Label=ARD_D10 [SPI_SSN]
PA2.GPIO_ModeDefaultOutputPP=GPIO_MODE_OUTPUT_PP
PA2.GPIO_PuPd=GPIO_NOPULL
PA2.GPIO_Speed=GPIO_SPEED_FREQ_LOW
PA2.PinState=GPIO_PIN_RESET
PA2.Signal=GPIO_Output
PA3.GPIOParameters=GPIO_Label
PA3.GPIO_Label=DISPL_LED
PA3.Signal=GPIO_Output
PA4.GPIOParameters=GPIO_Label
PA4.GPIO_Label=DISPL_CS
PA4.Mode=NSS_Signal_Hard_Output
PA4.Signal=SPI1_NSS
PA5.GPIOParameters=GPIO_Speed,GPIO_PuPd,GPIO_Label,GPIO_Mode
PA5.GPIO_Label=DISPL_SCK
PA5.GPIO_Mode=GPIO_MODE_AF_PP
PA5.GPIO_PuPd=GPIO_NOPULL
PA5.GPIO_Speed=GPIO_SPEED_FREQ_VERY_HIGH
PA5.Mode=Simplex_Bidirectional_Master
PA5.Signal=SPI1_SCK
PA6.GPIOParameters=GPIO_Label
PA6.GPIO_Label=BtnA
PA6.Signal=GPIO_Input
PA7.GPIOParameters=GPIO_Speed,GPIO_PuPd,GPIO_Label,GPIO_Mode
PA7.GPIO_Label=DISPL_MOSI
PA7.GPIO_Mode=GPIO_MODE_AF_PP
PA7.GPIO_PuPd=GPIO_NOPULL
PA7.GPIO_Speed=GPIO_SPEED_FREQ_VERY_HIGH
PA7.Mode=Simplex_Bidirectional_Master
PA7.Signal=SPI1_MOSI
PA8.GPIOParameters=GPIO_Speed,PinState,GPIO_PuPd,GPIO_Label,GPIO_ModeDefaultOutputPP
PA8.GPIO_Label=SPBTLE_RF_RST
PA8.GPIO_ModeDefaultOutputPP=GPIO_MODE_OUTPUT_PP
PA8.GPIO_PuPd=GPIO_NOPULL
PA8.GPIO_Speed=GPIO_SPEED_FREQ_LOW
PA8.PinState=GPIO_PIN_RESET
PA8.Signal=GPIO_Output
PA9.GPIOParameters=GPIO_PuPd,GPIO_Label,GPIO_Mode
PA9.GPIO_Label=USB_OTG_FS_VBUS
PA9.GPIO_Mode=GPIO_MODE_INPUT
PA9.GPIO_PuPd=GPIO_NOPULL
PA9.Signal=USB_OTG_FS_VBUS
PB0.GPIOParameters=GPIO_Label
PB0.GPIO_Label=DISPL_DC
PB0.Signal=GPIO_Output
PB1.GPIOParameters=GPIO_Label
PB1.GPIO_Label=DISPL_RST
PB1.Signal=GPIO_Output
PB10.GPIOParameters=GPIO_Speed,GPIO_PuPdOD,GPIO_Label,GPIO_Mode
PB10.GPIO_Label=INTERNAL_I2C2_SCL [MEMs]
PB10.GPIO_Mode=GPIO_MODE_AF_OD
PB10.GPIO_PuPdOD=GPIO_PULLUP
PB10.GPIO_Speed=GPIO_SPEED_FREQ_VERY_HIGH
PB10.Signal=I2C2_SCL
PB11.GPIOParameters=GPIO_Speed,GPIO_PuPdOD,GPIO_Label,GPIO_Mode
PB11.GPIO_Label=INTERNAL_I2C2_SDA [MEMs]
PB11.GPIO_Mode=GPIO_MODE_AF_OD
PB11.GPIO_PuPdOD=GPIO_PULLUP
PB11.GPIO_Speed=GPIO_SPEED_FREQ_VERY_HIGH
PB11.Signal=I2C2_SDA
PB12.GPIOParameters=GPIO_Speed,PinState,GPIO_PuPd,GPIO_Label,GPIO_ModeDefaultOutputPP
PB12.GPIO_Label=ISM43362_BOOT0
PB12.GPIO_ModeDefaultOutputPP=GPIO_MODE_OUTPUT_PP
PB12.GPIO_PuPd=GPIO_NOPULL
PB12.GPIO_Speed=GPIO_SPEED_FREQ_LOW
PB12.PinState=GPIO_PIN_RESET
PB12.Signal=GPIO_Output
PB13.GPIOParameters=GPIO_Speed,PinState,GPIO_PuPd,GPIO_Label,GPIO_ModeDefaultOutputPP
PB13.GPIO_Label=ISM43362_WAKEUP
PB13.GPIO_ModeDefaultOutputPP=GPIO_MODE_OUTPUT_PP
PB13.GPIO_PuPd=GPIO_NOPULL
PB13.GPIO_Speed=GPIO_SPEED_FREQ_LOW
PB13.PinState=GPIO_PIN_RESET
PB13.Signal=GPIO_Output
PB14.GPIOParameters=GPIO_Speed,PinState,GPIO_PuPd,GPIO_Label,GPIO_ModeDefaultOutputPP
PB14.GPIO_Label=LED2 [LED_GREEN]
PB14.GPIO_ModeDefaultOutputPP=GPIO_MODE_OUTPUT_PP
PB14.GPIO_PuPd=GPIO_NOPULL
PB14.GPIO_Speed=GPIO_SPEED_FREQ_LOW
PB14.PinState=GPIO_PIN_RESET
PB14.Signal=GPIO_Output
PB15.GPIOParameters=GPIO_Label
PB15.GPIO_Label=SPSGRF_915_SDN [SPSGRF_SDN]
PB15.Signal=GPIO_Output
PB2.GPIOParameters=GPIO_Label
PB2.GPIO_Label=BtnC
PB2.Signal=GPIO_Input
PB3\ (JTDO/TRACESWO).GPIOParameters=GPIO_Label
PB3\ (JTDO/TRACESWO).GPIO_Label=SYS_JTD0_SWO
PB3\ (JTDO/TRACESWO).Signal=SYS_JTDO-SWO
PB4\ (NJTRST).GPIOParameters=GPIO_Speed,PinState,GPIO_PuPd,GPIO_Label,GPIO_ModeDefaultOutputPP
PB4\ (NJTRST).GPIO_Label=ARD_D5
PB4\ (NJTRST).GPIO_ModeDefaultOutputPP=GPIO_MODE_OUTPUT_PP
PB4\ (NJTRST).GPIO_PuPd=GPIO_NOPULL
PB4\ (NJTRST).GPIO_Speed=GPIO_SPEED_FREQ_LOW
PB4\ (NJTRST).PinState=GPIO_PIN_RESET
PB4\ (NJTRST).Signal=GPIO_Output
PB5.GPIOParameters=GPIO_Label
PB5.GPIO_Label=SPSGRF_915_SPI3_CSN [SPSGRF_SPI_CS]
PB5.Signal=GPIO_Output
PB6.GPIOParameters=GPIO_ModeDefaultPP,GPIO_Speed,GPIO_FM6,GPIO_PuPd,GPIO_Label
PB6.GPIO_FM6=__NULL
PB6.GPIO_Label=ST-LINK-UART1_TX
PB6.GPIO_ModeDefaultPP=GPIO_MODE_AF_PP
PB6.GPIO_PuPd=GPIO_NOPULL
PB6.GPIO_Speed=GPIO_SPEED_FREQ_VERY_HIGH
PB6.Signal=USART1_TX
PB7.GPIOParameters=GPIO_ModeDefaultPP,GPIO_Speed,GPIO_PuPd,GPIO_Label,GPIO_FM7
PB7.GPIO_FM7=__NULL
PB7.GPIO_Label=ST_LINK_UART1_RX
PB7.GPIO_ModeDefaultPP=GPIO_MODE_AF_PP
PB7.GPIO_PuPd=GPIO_NOPULL
PB7.GPIO_Speed=GPIO_SPEED_FREQ_VERY_HIGH
PB7.Signal=USART1_RX
PB8.GPIOParameters=GPIO_Speed,GPIO_PuPdOD,GPIO_Label,GPIO_FM8,GPIO_Mode
PB8.GPIO_FM8=__NULL
PB8.GPIO_Label=ARD_D15 [I2C1_SCL]
PB8.GPIO_Mode=GPIO_MODE_AF_OD
PB8.GPIO_PuPdOD=GPIO_PULLUP
PB8.GPIO_Speed=GPIO_SPEED_FREQ_VERY_HIGH
PB8.Signal=I2C1_SCL
PB9.GPIOParameters=GPIO_Speed,GPIO_PuPdOD,GPIO_Label,GPIO_Mode,GPIO_FM9
PB9.GPIO_FM9=__NULL
PB9.GPIO_Label=ARD_D14 [I2C1_SDA]
PB9.GPIO_Mode=GPIO_MODE_AF_OD
PB9.GPIO_PuPdOD=GPIO_PULLUP
PB9.GPIO_Speed=GPIO_SPEED_FREQ_VERY_HIGH
PB9.Signal=I2C1_SDA
PC0.GPIOParameters=GPIO_PuPd,GPIO_Label,GPIO_Mode
PC0.GPIO_Label=ARD_A5 [ADC]
PC0.GPIO_Mode=GPIO_MODE_ANALOG_ADC_CONTROL
PC0.GPIO_PuPd=GPIO_NOPULL
PC0.Signal=ADCx_IN1
PC1.GPIOParameters=GPIO_PuPd,GPIO_Label,GPIO_Mode
PC1.GPIO_Label=ARD_A4 [ADC]
PC1.GPIO_Mode=GPIO_MODE_ANALOG_ADC_CONTROL
PC1.GPIO_PuPd=GPIO_NOPULL
PC1.Signal=ADCx_IN2
PC10.GPIOParameters=GPIO_Speed,GPIO_PuPd,GPIO_Label,GPIO_Mode
PC10.GPIO_Label=INTERNAL-SPI3_SCK [BT module_SPI_MOSI] [ISM43362_MOSI]
PC10.GPIO_Mode=GPIO_MODE_AF_PP
PC10.GPIO_PuPd=GPIO_NOPULL
PC10.GPIO_Speed=GPIO_SPEED_FREQ_VERY_HIGH
PC10.Mode=Simplex_Bidirectional_Master
PC10.Signal=SPI3_SCK
PC11.GPIOParameters=GPIO_Speed,GPIO_PuPd,GPIO_Label,GPIO_Mode
PC11.GPIO_Label=INTERNAL_SPI3_MISO [BT module_SPI_MOSI] [ISM43362_MOSI]
PC11.GPIO_Mode=GPIO_MODE_AF_PP
PC11.GPIO_PuPd=GPIO_NOPULL
PC11.GPIO_Speed=GPIO_SPEED_FREQ_VERY_HIGH
PC11.Signal=SPI3_MISO
PC12.GPIOParameters=GPIO_Speed,GPIO_PuPd,GPIO_Label,GPIO_Mode
PC12.GPIO_Label=INTERNAL_SPI3_MOSI [BT module_SPI_MOSI] [ISM43362_MOSI]
PC12.GPIO_Mode=GPIO_MODE_AF_PP
PC12.GPIO_PuPd=GPIO_NOPULL
PC12.GPIO_Speed=GPIO_SPEED_FREQ_VERY_HIGH
PC12.Mode=Simplex_Bidirectional_Master
PC12.Signal=SPI3_MOSI
PC13.GPIOParameters=GPIO_PuPd,GPIO_Label,GPIO_ModeDefaultEXTI
PC13.GPIO_Label=BUTTON_EXTI13 [B2]
PC13.GPIO_ModeDefaultEXTI=GPIO_MODE_IT_RISING
PC13.GPIO_PuPd=GPIO_NOPULL
PC13.Signal=GPXTI13
PC2.GPIOParameters=GPIO_PuPd,GPIO_Label,GPIO_Mode
PC2.GPIO_Label=ARD_A3 [ADC]
PC2.GPIO_Mode=GPIO_MODE_ANALOG_ADC_CONTROL
PC2.GPIO_PuPd=GPIO_NOPULL
PC2.Signal=ADCx_IN3
PC3.GPIOParameters=GPIO_PuPd,GPIO_Label,GPIO_Mode
PC3.GPIO_Label=ARD_A2 [ADC]
PC3.GPIO_Mode=GPIO_MODE_ANALOG_ADC_CONTROL
PC3.GPIO_PuPd=GPIO_NOPULL
PC3.Signal=ADCx_IN4
PC4.GPIOParameters=GPIO_PuPd,GPIO_Label,GPIO_Mode
PC4.GPIO_Label=ARD_A1 [ADC]
PC4.GPIO_Mode=GPIO_MODE_ANALOG_ADC_CONTROL
PC4.GPIO_PuPd=GPIO_NOPULL
PC4.Signal=ADCx_IN13
PC5.GPIOParameters=GPIO_PuPd,GPIO_Label,GPIO_Mode
PC5.GPIO_Label=ARD_A0 [ADC]
PC5.GPIO_Mode=GPIO_MODE_ANALOG_ADC_CONTROL
PC5.GPIO_PuPd=GPIO_NOPULL
PC5.Signal=ADCx_IN14
PC6.GPIOParameters=GPIO_Speed,PinState,GPIO_PuPd,GPIO_Label,GPIO_ModeDefaultOutputPP
PC6.GPIO_Label=VL53L0X_XSHUT
PC6.GPIO_ModeDefaultOutputPP=GPIO_MODE_OUTPUT_PP
PC6.GPIO_PuPd=GPIO_NOPULL
PC6.GPIO_Speed=GPIO_SPEED_FREQ_LOW
PC6.PinState=GPIO_PIN_RESET
PC6.Signal=GPIO_Output
PC7.GPIOParameters=GPIO_PuPd,GPIO_Label,GPIO_ModeDefaultEXTI
PC7.GPIO_Label=VL53L0X_GPIO1_EXTI7
PC7.GPIO_ModeDefaultEXTI=GPIO_MODE_IT_RISING
PC7.GPIO_PuPd=GPIO_NOPULL
PC7.Signal=GPXTI7
PC8.GPIOParameters=GPIO_PuPd,GPIO_Label,GPIO_ModeDefaultEXTI
PC8.GPIO_Label=LSM3MDL_DRDY_EXTI8
PC8.GPIO_ModeDefaultEXTI=GPIO_MODE_IT_RISING
PC8.GPIO_PuPd=GPIO_NOPULL
PC8.Signal=GPXTI8
PC9.GPIOParameters=GPIO_Speed,PinState,GPIO_PuPd,GPIO_Label,GPIO_ModeDefaultOutputPP
PC9.GPIO_Label=LED3_WIFI_ LED4_BLE
PC9.GPIO_ModeDefaultOutputPP=GPIO_MODE_OUTPUT_PP
PC9.GPIO_PuPd=GPIO_NOPULL
PC9.GPIO_Speed=GPIO_SPEED_FREQ_LOW
PC9.PinState=GPIO_PIN_RESET
PC9.Signal=GPIO_Output
PD0.GPIOParameters=GPIO_Speed,PinState,GPIO_PuPd,GPIO_Label,GPIO_ModeDefaultOutputPP
PD0.GPIO_Label=PMOD_RESET
PD0.GPIO_ModeDefaultOutputPP=GPIO_MODE_OUTPUT_PP
PD0.GPIO_PuPd=GPIO_NOPULL
PD0.GPIO_Speed=GPIO_SPEED_FREQ_LOW
PD0.PinState=GPIO_PIN_RESET
PD0.Signal=GPIO_Output
PD1.GPIOParameters=GPIO_Label
PD1.GPIO_Label=PMOD_SPI2_SCK
PD1.Signal=GPIO_Output
PD10.GPIOParameters=GPIO_PuPd,GPIO_Label,GPIO_ModeDefaultEXTI
PD10.GPIO_Label=LPS22HB_INT_DRDY_EXTI10

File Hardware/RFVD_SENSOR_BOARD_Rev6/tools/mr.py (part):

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    'K16_DISP_LANE*': (['B.Cu'], ['CHG_INT_N', 'LCD_TE_MCU', '/Screen and controls/LCD_TE', '/STM32H743 controller/LCD_RST_MCU',
                                  'LCD_RST', '/STM32H743 controller/TP_RST_MCU', 'TP_RST', 'BUCK_SYNC',
                                  '/STM32H743 controller/BUCK_SYNC_MCU'], None),
    'K17_LSE_GUARD*': (['B.Cu'], ['Net-(U8-PC14)', 'Net-(U8-PC15)', 'GND'], None),
    'K19?_VSYS*': (['B.Cu'], ['VSYS'], ['VSYS', 'GND']),
    'K20a_EREF_LANE*': (['B.Cu'], ['ADC_EREF'], None),
    'K20b_VENV_LANE*': (['B.Cu'], ['ADC_VENV'], None),
    'K10F_HSE_CELL*': (['F.Cu'], ['+3V3_D', 'GND', 'Net-(Y1-OUT)', 'Net-(U8-PH0)'], ['+3V3_D', 'GND']),
    'K10B_HSE_SHADOW*': (['B.Cu'], [], ['GND']),
    'K6_B_RF_END*': (['B.Cu'], [], ['GND']),
    'K11_*': (['F.Cu'], ['GND'], ['GND']),
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    if {n, m} == {'+3V3_D', '+3V3_A'} and 'FB' not in ex:
        c = max(c, 2.0)
    # v7_emc05_buck_sync_lse_3mm (EMC-05): the buck SYNC clock (both sides of R901) >= 3 mm from the LSE crystal nets
    if ({n.split('/')[-1], m.split('/')[-1]} & {'BUCK_SYNC', 'BUCK_SYNC_MCU'}) and             ({n, m} & {'Net-(U8-PC14)', 'Net-(U8-PC15)'}):
        c = max(c, 3.0)
    return c

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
